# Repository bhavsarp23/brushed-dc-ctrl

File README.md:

# brushed-dc-ctrl
Simple Brushed DC Motor Controller

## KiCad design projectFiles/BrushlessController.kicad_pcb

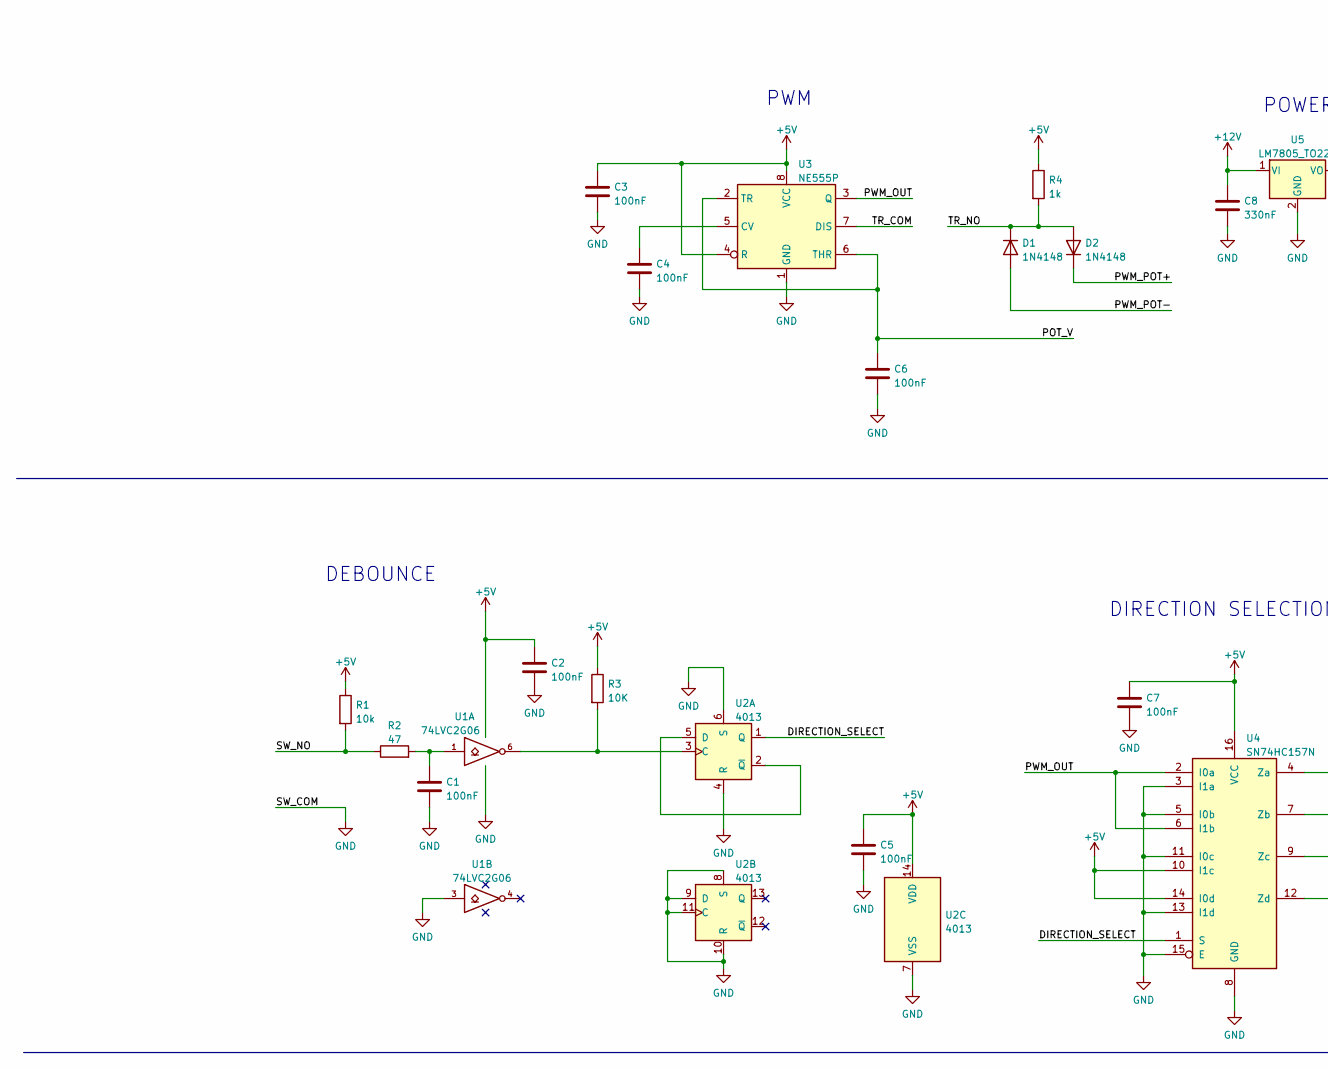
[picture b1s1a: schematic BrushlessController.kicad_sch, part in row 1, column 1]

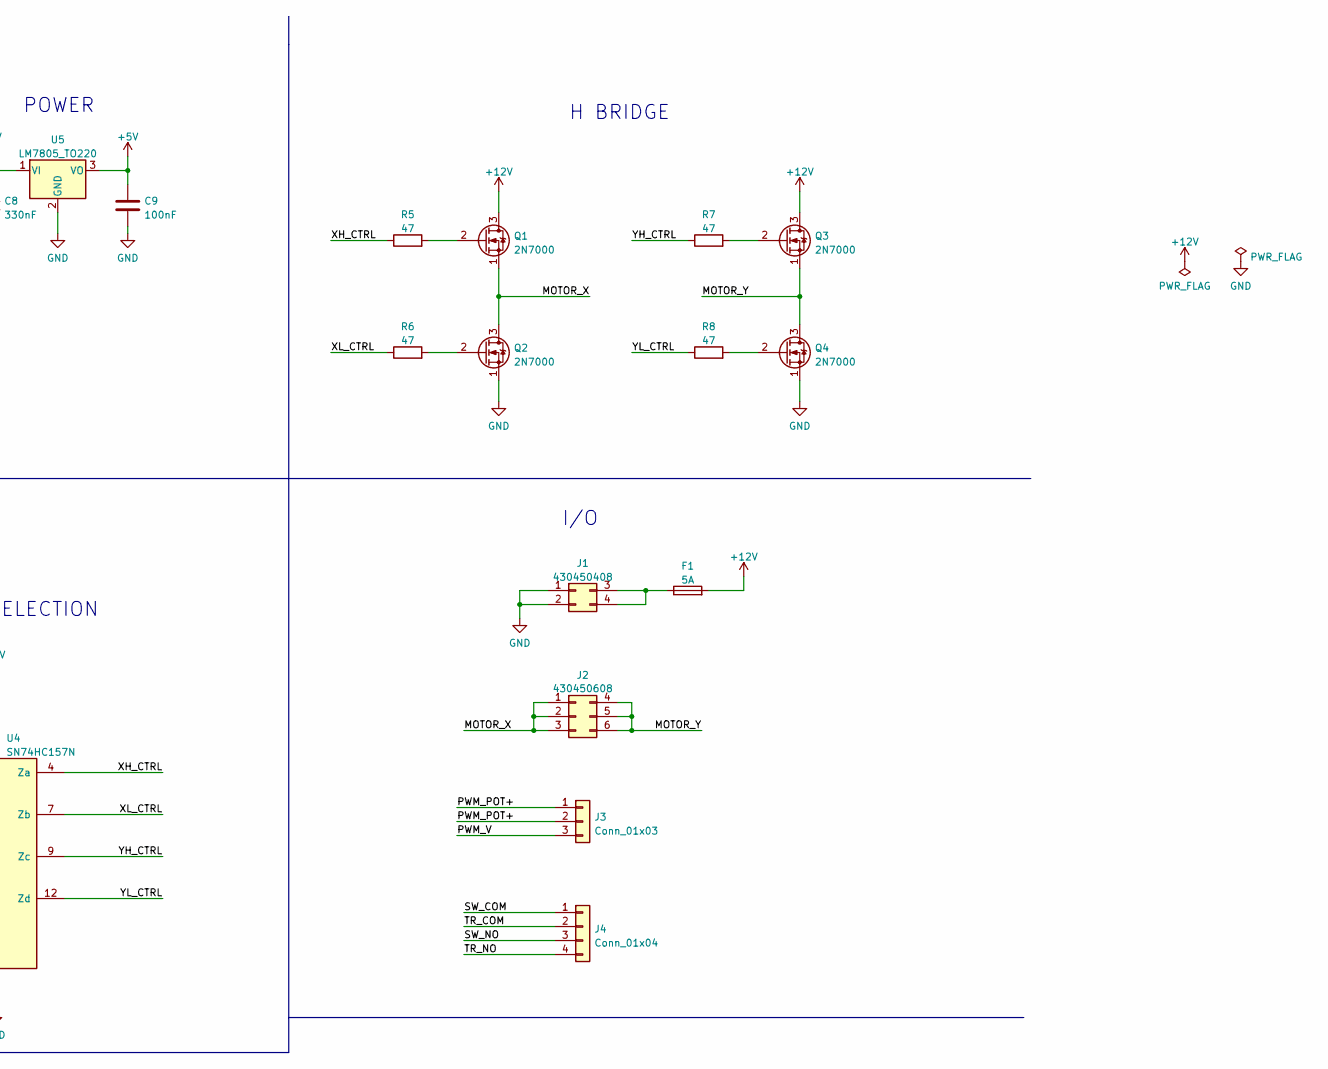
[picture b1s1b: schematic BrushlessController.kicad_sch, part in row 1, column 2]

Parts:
C1, C2, C3, C4, C5, C6, C7, C9: 100nF; C_0805_2012Metric_Pad1.18x1.45mm_HandSolder
C8: 330nF; C_0805_2012Metric_Pad1.18x1.45mm_HandSolder
D1, D2: 1N4148; D_DO-35_SOD27_P7.62mm_Horizontal
F1: 5A; Fuse_Blade_Mini_directSolder
J1: 430450408; Molex_Micro-Fit_3.0_43045-0412_2x02_P3.00mm_Vertical
J2: 430450608; Molex_Micro-Fit_3.0_43045-0612_2x03_P3.00mm_Vertical
J3: Conn_01x03; Molex_Micro-Fit_3.0_43650-0315_1x03_P3.00mm_Vertical
J4: Conn_01x04; Molex_Micro-Fit_3.0_43650-0415_1x04_P3.00mm_Vertical
Q1, Q2, Q3, Q4: 2N7000; TO-92_Inline
R1: 10k; R_0805_2012Metric_Pad1.20x1.40mm_HandSolder
R2, R5, R6, R7, R8: 47; R_0805_2012Metric_Pad1.20x1.40mm_HandSolder
R3: 10K; R_0805_2012Metric_Pad1.20x1.40mm_HandSolder
R4: 1k; R_0805_2012Metric_Pad1.20x1.40mm_HandSolder
U1: 74LVC2G06; SOT-363_SC-70-6_Handsoldering
U2: 4013; DIP-14_W7.62mm
U3: NE555P; DIP-8_W7.62mm
U4: SN74HC157N; DIP-16_W7.62mm
U5: LM7805_TO220; TO-220-3_Vertical

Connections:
+12V: C8.1, F1.2, Q1.3 (D), Q3.3 (D), U5.1 (VI)
/DIRECTION_SELECT: U2.1 (Q), U4.1 (S)
/MOTOR_X: J2.1, J2.2, J2.3, Q1.1 (S), Q2.3 (D)
/MOTOR_Y: J2.4, J2.5, J2.6, Q3.1 (S), Q4.3 (D)
/POT_V: C6.1, U3.2 (TR), U3.6 (THR)
/PWM_OUT: U3.3 (Q), U4.2 (I0a), U4.6 (I1b)
/PWM_POT+: D2.1 (K), J3.1, J3.2
/PWM_POT-: D1.2 (A)
/PWM_V: J3.3
/SW_NO: J4.3, R1.2, R2.1
/TR_COM: J4.2, U3.7 (DIS)
/TR_NO: D1.1 (K), D2.2 (A), J4.4, R4.2
/XH_CTRL: R5.1, U4.4 (Za)
/XL_CTRL: R6.1, U4.7 (Zb)
/YH_CTRL: R7.1, U4.9 (Zc)
/YL_CTRL: R8.1, U4.12 (Zd)
GND: C1.2, C2.2, C3.2, C4.2, C5.2, C6.2, C7.2, C8.2, C9.2, J1.1, J1.2, J4.1, Q2.1 (S), Q4.1 (S), U1.2 (GND), U1.3, U2.4 (R), U2.6 (S), U2.7 (VSS), U2.8 (S), U2.9 (D), U2.10 (R), U2.11 (C), U3.1 (GND), U4.3 (I1a), U4.5 (I0b), U4.8 (GND), U4.11 (I0c), U4.13 (I1d), U4.15 (E), U5.2 (GND)
unnamed: C1.1, R2.2, U1.1
unnamed: C4.1, U3.5 (CV)
unnamed: F1.1, J1.3, J1.4
unnamed: Q1.2 (G), R5.2
unnamed: Q2.2 (G), R6.2
unnamed: Q3.2 (G), R7.2
unnamed: Q4.2 (G), R8.2
unnamed: R3.2, U1.6, U2.3 (C)
unnamed: U2.2 (~Q), U2.5 (D)
VCC: C2.1, C3.1, C5.1, C7.1, C9.1, R1.1, R3.1, R4.1, U1.5 (VCC), U2.14 (VDD), U3.4 (R), U3.8 (VCC), U4.10 (I1c), U4.14 (I0d), U4.16 (VCC), U5.3 (VO)

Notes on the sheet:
H BRIDGE
POWER
I/O
DEBOUNCE
PWM
DIRECTION SELECTION

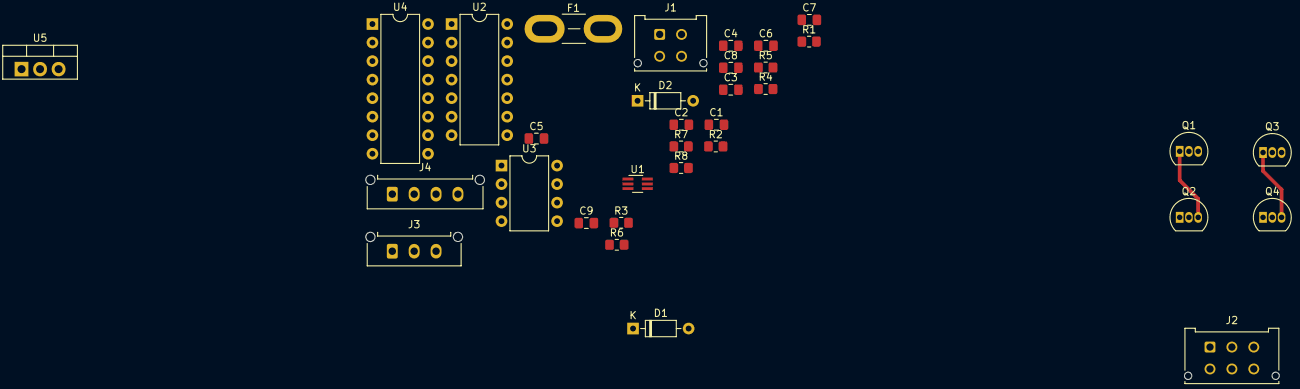
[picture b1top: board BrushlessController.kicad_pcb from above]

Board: 2 copper layers, 33 parts (0 on the bottom side), 25 nets.

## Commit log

2022-09-16 Rename BrushlessController.kicad_pcb to BrushedDCCtrl.kicad_pcb
2022-09-16 Rename BrushlessController.kicad_prl to BrushedDCCtrl.kicad_prl
2022-09-16 Rename BrushlessController.kicad_sch to BrushedDCCtrl.kicad_sch
2022-09-17 Rename BrushlessController-B_Cu.gbr to BrushedDCCtrl-B_Cu.gbr
